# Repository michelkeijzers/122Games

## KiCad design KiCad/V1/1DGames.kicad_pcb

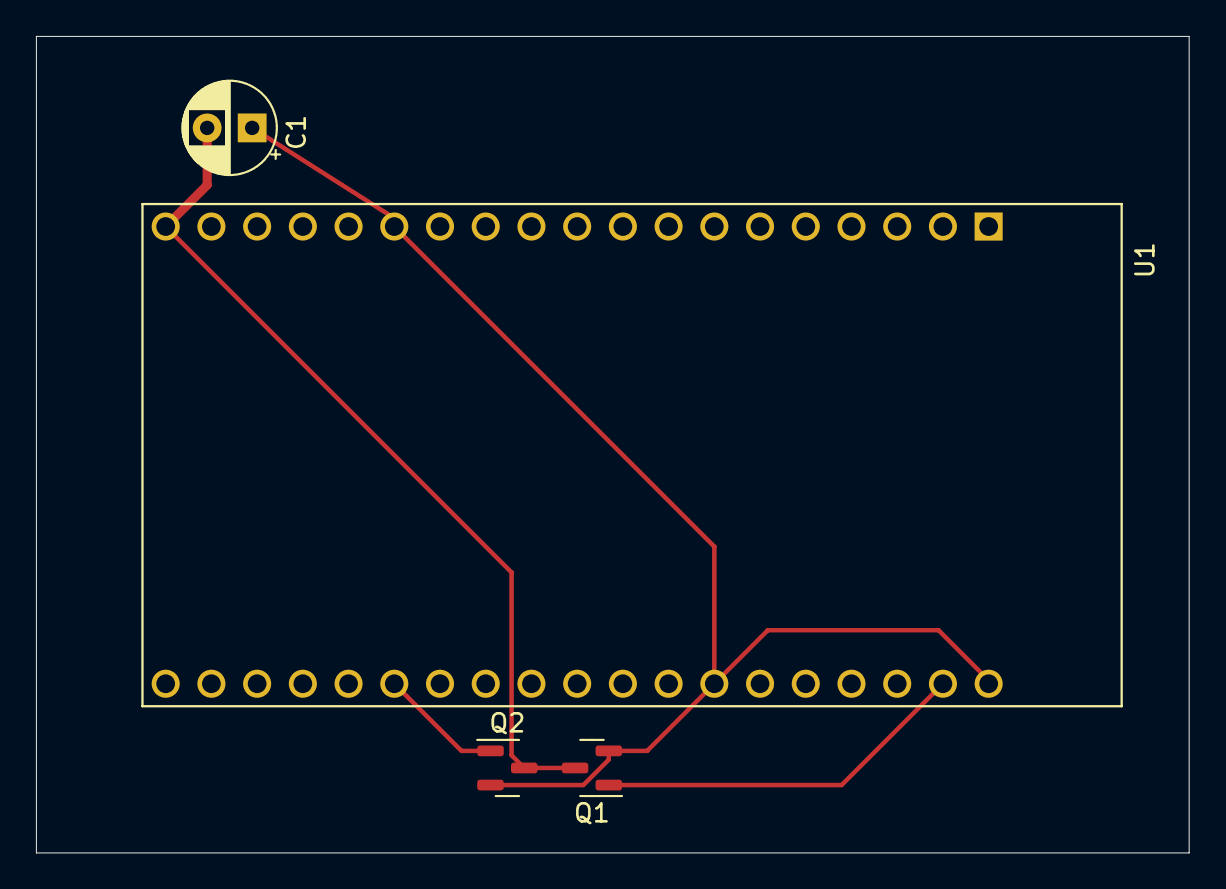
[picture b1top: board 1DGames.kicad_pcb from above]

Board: 2 copper layers, 64.0 x 45.4 mm, 4 parts (0 on the bottom side), 4 nets.

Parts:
C1: 470uF; CP_Radial_D5.0mm_P2.50mm
Q1, Q2: AO3401A; SOT-23
U1: ESP32-DEVKITC-32D; MODULE_ESP32-DEVKITC-32D

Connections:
/+5V: C1.2, Q1.3 (D), Q2.3 (D), U1.19 (EXT_5V)
/LED_STRIP_DATA: Q2.1 (G), U1.33 (IO0)
/SPEAKER_IN: Q1.1 (G), U1.21 (IO23)
GND: C1.1, Q1.2 (S), Q2.2 (S), U1.14 (GND1), U1.20 (GND3), U1.26 (GND2)

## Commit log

2022-06-09 Add .gitignore and .gitattributes.
2022-06-09 Add project files.
2022-06-09 Fixed git repository
2022-06-13 New architecture
2022-06-16 Changed Led strip class, UI modules in general
2022-06-16 First version of FourDigitsLed and TM1637Display(Stub)
2022-06-22 User interface changes, added tone/speaker
2022-06-26 Worms joystick working, next: show joystick status in UI (including button).
2022-06-27 LEDs for Worms and Joystick on GUI
2022-06-28 Added button.
2022-06-28 Moved code to Game class
2022-06-28 Non diagonal directions for Joystick.
2022-06-28 Renamed JoyStick class to Joystick
2022-06-28 Renamed JoyStick to Joystick part two.
2022-06-29 Performance of CppScreen improved.
2022-06-30 Compilable for Arduino Uno
2022-06-30 Compiles for ESP32
2022-06-30 LCD Display support (and Print class), removed Canvas, LedSEgments and Max7219
2022-07-01 Electronic scheme, program for calculating LED coordinates.
2022-07-01 Added main buttons.
2022-07-02 Fixed sound/buttons.
2022-07-04 Menu
2022-07-04 Menu working to Worms game, but 2 times select button is needed.
2022-07-04 Menu and game fixes.
2022-07-05 Reduced line length to 100
2022-07-05 Fixed /improved formulas
